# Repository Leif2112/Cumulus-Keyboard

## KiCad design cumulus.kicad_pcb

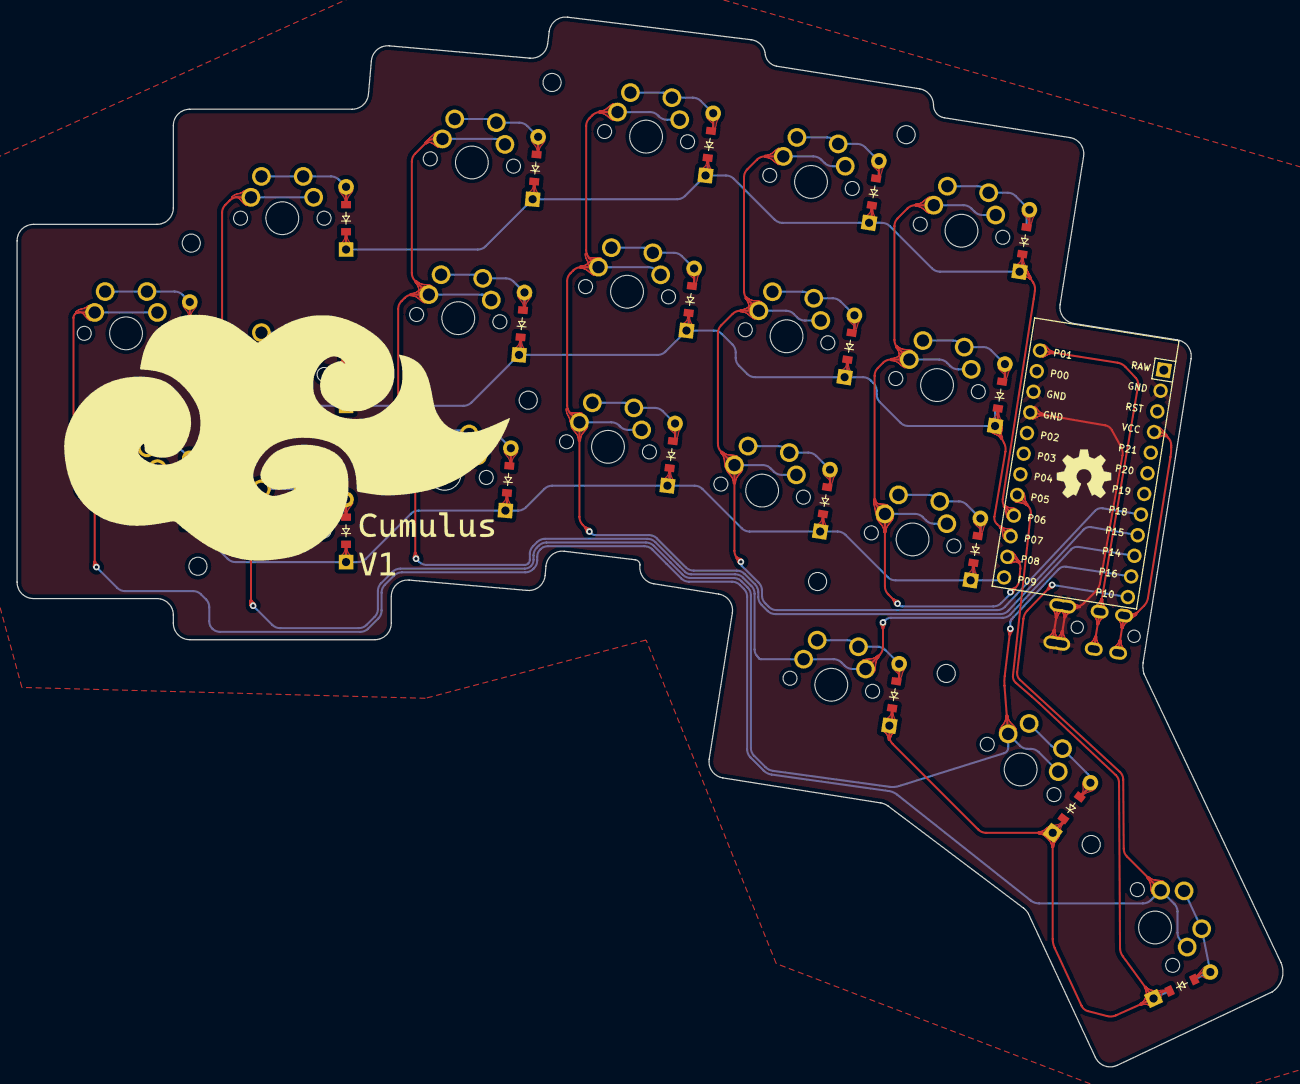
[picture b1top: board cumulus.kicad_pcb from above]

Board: 2 copper layers, 153.9 x 127.6 mm, 41 parts (0 on the bottom side), 31 nets.

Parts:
D1, D2, D3, D4, D5, D6, D7, D8, D9, D10, D11, D12, D13, D14, D15, D16, D17, D18, D19, D20: ComboDiode
MCU1: ProMicro
S1, S2, S3, S4, S5, S6, S7, S8, S9, S10, S11, S12, S13, S14, S15, S16, S17, S18, S19, S20: MX

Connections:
GND: MCU1.2, MCU1.15, MCU1.16
P5: D16.1, D16.2, D17.1, D17.2, D18.1, D18.2, MCU1.20
P6: D3.1, D3.2, D6.1, D6.2, D9.1, D9.2, D12.1, D12.2, D15.1, D15.2, MCU1.21
P7: D2.1, D2.2, D5.1, D5.2, D8.1, D8.2, D11.1, D11.2, D14.1, D14.2, D20.1, D20.2, MCU1.22
P8: MCU1.23, S13.2, S14.2, S15.2
P9: D1.1, D1.2, D4.1, D4.2, D7.1, D7.2, D10.1, D10.2, D13.1, D13.2, D19.1, D19.2, MCU1.24
P10: MCU1.12, S18.2, S19.2, S20.2
P14: MCU1.10, S4.2, S5.2, S6.2, S16.2
P15: MCU1.9, S7.2, S8.2, S9.2
P16: MCU1.11, S1.2, S2.2, S3.2, S17.2
P18: MCU1.8, S10.2, S11.2, S12.2
default_m1: D19.1, D19.2, S19.1
default_m2: D20.1, D20.2, S20.1
far_thumb: D18.1, D18.2, S18.1
home_thumb: D17.1, D17.2, S17.1
index_bottom: D10.1, D10.2, S10.1
index_home: D11.1, D11.2, S11.1
index_top: D12.1, D12.2, S12.1
inner_bottom: D13.1, D13.2, S13.1
inner_home: D14.1, D14.2, S14.1
inner_top: D15.1, D15.2, S15.1
middle_bottom: D7.1, D7.2, S7.1
middle_home: D8.1, D8.2, S8.1
middle_top: D9.1, D9.2, S9.1
near_thumb: D16.1, D16.2, S16.1
pinky_bottom: D1.1, D1.2, S1.1
pinky_home: D2.1, D2.2, S2.1
pinky_top: D3.1, D3.2, S3.1
ring_bottom: D4.1, D4.2, S4.1
ring_home: D5.1, D5.2, S5.1
ring_top: D6.1, D6.2, S6.1

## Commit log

2022-08-16 Initialize project
2022-08-16 Add submodules
2022-08-24 Add submodules bis
2022-08-26 Ergogen -> Kicad
2022-08-26 Reversible ProMicro footprint added
2022-08-29 Adafruit KB2040 files
2022-08-29 W.I.P
2022-08-30 PCB routing finished
2022-08-30 Logo + PCB fill zone
2022-08-30 Drill files generated
2022-09-06 Initial Firmware commit
2022-09-08 3D models
2022-09-09 Fusion360 Model archive
2022-09-12 Plate re-design
